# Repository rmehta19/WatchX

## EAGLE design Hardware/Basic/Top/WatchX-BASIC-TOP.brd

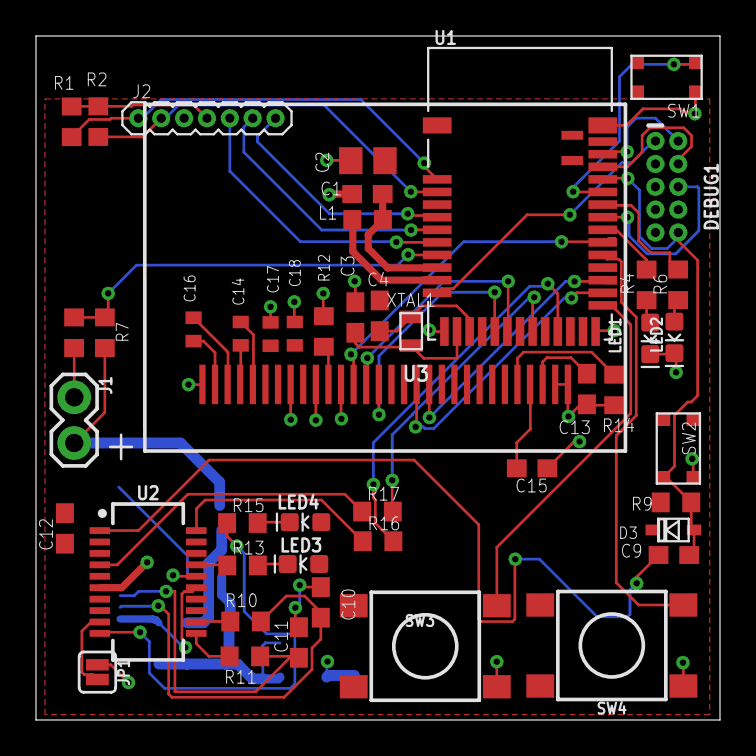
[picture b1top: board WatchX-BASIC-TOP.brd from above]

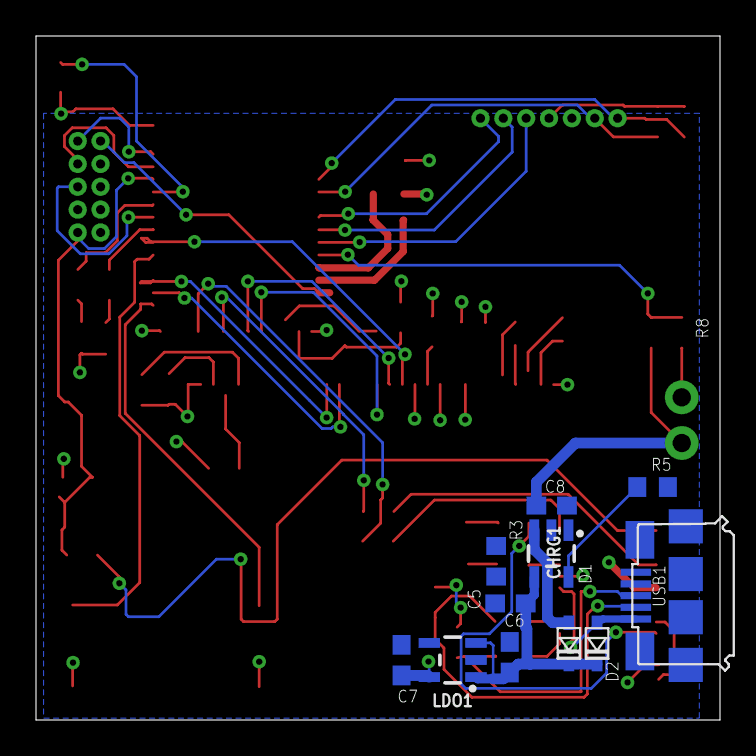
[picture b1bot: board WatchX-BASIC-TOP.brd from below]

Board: 2 copper layers, 38.0 x 38.0 mm, 58 parts (11 on the bottom side), 55 nets.

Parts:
C1, C6, C7: 1u; C0603
C2: 10u; C0805
C3, C4: C0603
C5, C8: 4.7u; C0603
C9, C12: 100n; C0603
C10, C11: 47p; C0603
C13: 10uF; C0603
C14, C16, C17, C18: 2.2uF; C0402
C15: 2.2uF; C0603
CHRG1: MCP73831; SOT23-5
D1, D2, D3: USC
DEBUG1: CORTEX_DEBUG_PTH; 2X5-PTH-1.27MM
J1: 1X02
J2: 1X07_1.27MM
JP1: SMT-JUMPER_2_NO_SILK
L1: 10u; L0603
LDO1: MIC5504; SOT23-5
LED1, LED3: RED; LED-0603
LED2: BLUE; LED-0603
LED4: YELLOW; LED-0603
R1, R2, R9, R12: 10k; R0603
R3, R7, R8: 100k; R0603
R4, R6, R13, R15: 1k; R0603
R5: 5k; R0603
R10, R11: 27; R0603
R14: 390k; R0603
R16, R17: R0603
SW1, SW2: BUTTON-GULLWING
SW3, SW4: SWITCH.MOM; TACTILE_SWITCH_SMD_6.2MM_TALL
U1: NRF52832_MODULE_MDBT42; BLE_MODULE_RAYTAC_MDBT42
U2: FT231XS; SSOP20_L
U3: UG-2864HSWEG01_0.96IN_NO-WRAPAROUND
USB1: USB.MICRO-BIGGERPADS; USB-MICRO-01.BIGGERPADS
XTAL1: 32.768kHz; 2-SMD.NOLEAD.2.0MMTO1.2MM

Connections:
3.3V: C2.2, C7.1, C12.2, C17.2, C18.2, D3.-, DEBUG1.1, J2.4, LDO1.5, LED3.A, LED4.A, R1.2, R2.2, R9.2, U1.11, U2.3, U2.14, U3.6, U3.9
!CTS: JP1.2, U2.9
A4/PPG: J2.7, U1.5
A5/TIA: J2.6, U1.6
A7/BATT: R7.1, R8.2, U1.8
D3/RESET.OLED: U1.17, U3.14
D4/DC.OLED: U1.16, U3.15
D11/SW1: SW3.A1, U1.25
D15/SW2: SW4.A1, U1.29
D16/CS.OLED: U1.30, U3.13
D27/CHRG.STAT: CHRG1.1, R3.1
D30/LED.CTRL: J2.5, U1.7
DFU: SW1.3, U1.34
DTR: C9.1, U2.1
GND: C1.2, C2.1, C3.1, C4.2, C5.1, C6.1, C7.2, C8.2, C10.1, C11.2, C12.1, C13.1, C15.1, C17.1, C18.1, CHRG1.2, DEBUG1.3, DEBUG1.5, DEBUG1.7, DEBUG1.9, J1.1, J2.3, JP1.1, LDO1.2, LED1.C, LED2.C, R5.1, R8.1, R12.1, R14.2, SW1.1, SW2.3, SW3.B1, SW3.B2, SW4.B1, SW4.B2, U1.1, U1.12, U1.24, U1.39, U2.6, U2.16, U3.1, U3.8, U3.10, U3.12, U3.29, U3.30, USB1.5, USB1.S1, USB1.S2, USB1.S3, USB1.S4, USB1.S5, USB1.S6
LED1: R4.2, U1.31
LED2: R6.2, U1.33
MOSI: U1.27, U3.19
unnamed: R12.2, U3.11
unnamed: R14.1, U3.26
unnamed: C16.2, U3.2
unnamed: C3.2, U1.13, XTAL1.P$1
unnamed: C16.1, U3.3
unnamed: C4.1, U1.14, XTAL1.P$2
unnamed: C14.2, U3.4
unnamed: C14.1, U3.5
unnamed: LED1.A, R4.1
unnamed: LED2.A, R6.1
unnamed: L1.1, U1.10
unnamed: C1.1, L1.2, U1.9
unnamed: C13.2, U3.28
unnamed: C15.2, U3.27
unnamed: CHRG1.5, R5.2
unnamed: R10.2, U2.12
unnamed: R11.2, U2.11
unnamed: LED3.C, R13.2
unnamed: LED4.C, R15.2
RESET: C9.2, D3.+, DEBUG1.10, R9.1, SW2.1, U1.35
RXD.FT: R17.1, U2.4
RXD.NRF: R16.2, U1.21
RXLED: R13.1, U2.17
SCK: U1.26, U3.18
SCL: J2.2, R2.1, U1.3
SDA: J2.1, R1.1, U1.2
SWCLK: DEBUG1.4, U1.36
SWDIO: DEBUG1.2, U1.37
SWO: DEBUG1.6, U1.32
TXD.FT: R16.1, U2.20
TXD.NRF: R17.2, U1.19
TXLED: R15.1, U2.10
USB+: C11.1, R11.1, USB1.3
USB-: C10.2, R10.1, USB1.2
VIN: C5.2, C6.2, CHRG1.4, D1.-, D2.-, LDO1.1, LDO1.3, R3.2
VLIPO: C8.1, CHRG1.3, D1.+, J1.2, R7.2
V_USB: D2.+, U2.15, USB1.1

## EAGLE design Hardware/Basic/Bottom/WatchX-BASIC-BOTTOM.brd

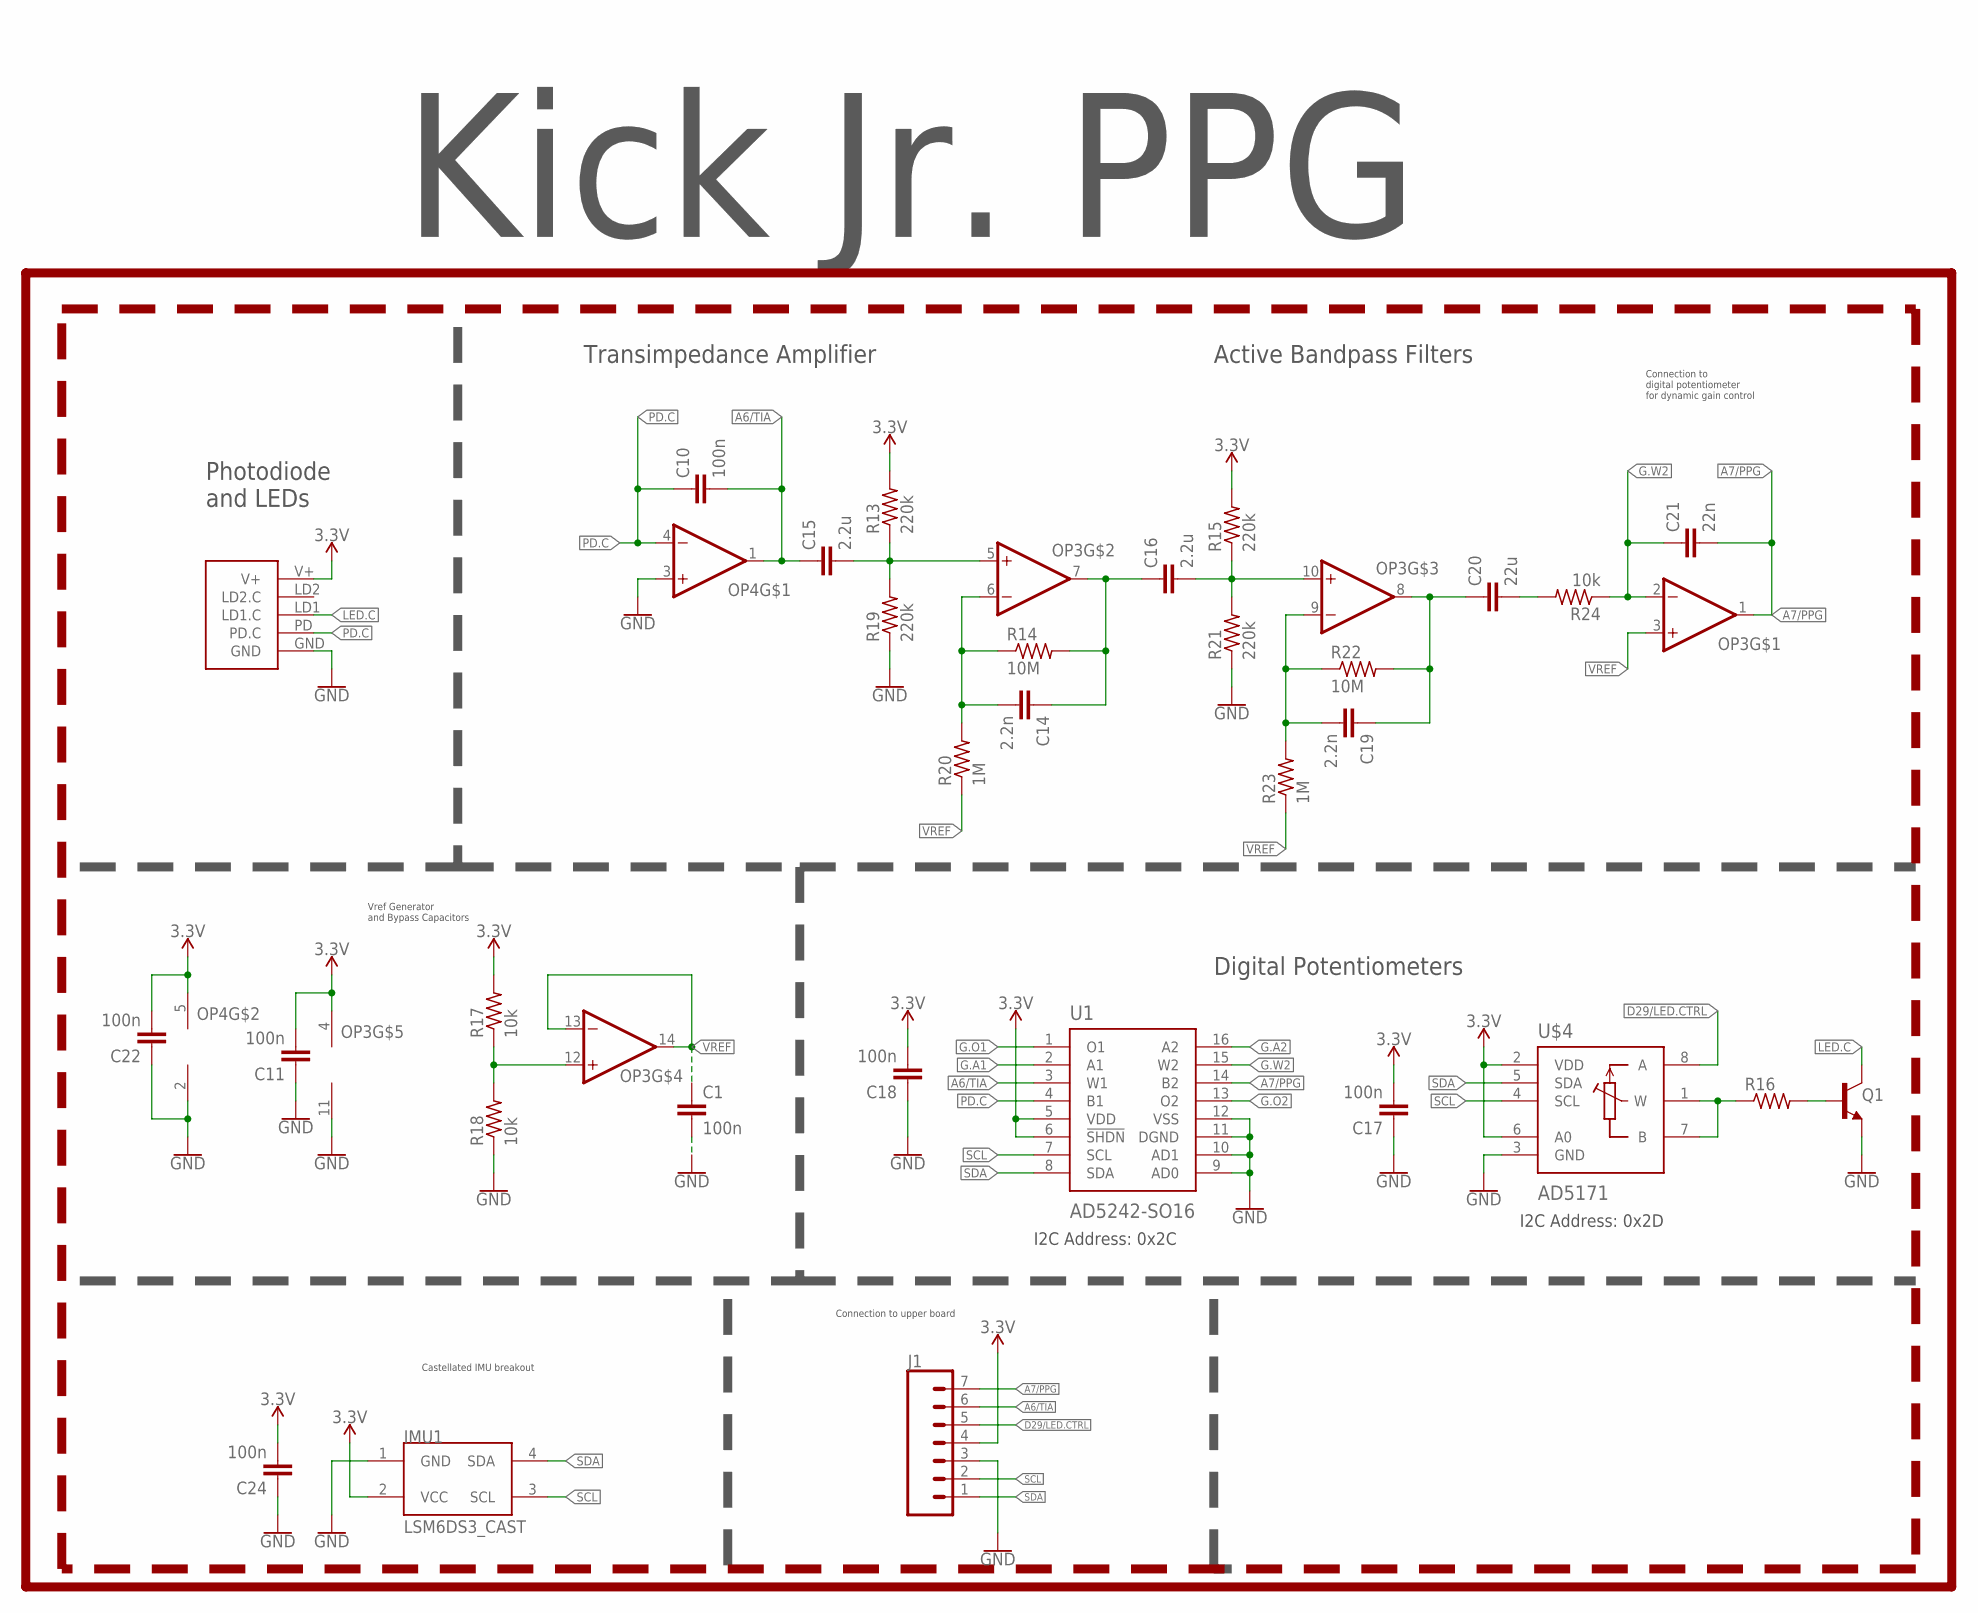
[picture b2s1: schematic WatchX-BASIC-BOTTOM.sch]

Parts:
C1, C10, C11, C17, C18, C22, C24: 100n; C0603
C14, C19: 2.2n; C0603
C15, C16: 2.2u; C0603
C20: 22u; C0603
C21: 22n; C0603
IMU1: LSM6DS3_CAST
J1: CONN_07-1.27MM; 1X07_1.27MM
OP3: OP-QUAD-SO14; SO14
OP4: OP-SINGLEOT; SOT23-5
Q1: NPN-GENERIC; SOT23-3
R13, R15, R19, R21: 220k; R0603
R14, R22: 10M; R0603
R16: RESISTOR0603; R0603
R17, R18: 10k; R0402
R20, R23: 1M; R0603
R24: 10k; R0603
U1: AD5242-SO16; SO16
U$3: PPG.MODULE.2
U$4: AD5171; SOT-23-8

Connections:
3.3V: C11.2, C17.2, C18.2, C22.2, C24.2, IMU1.2 (VCC), J1.4, OP3.4 (V+), OP4.5 (V+), R13.2, R15.2, R17.2, U1.5 (VDD), U1.6 (!SHDN), U$3.V+, U$4.2 (VDD), U$4.6 (A0)
A6/TIA: C10.2, C15.1, J1.6, OP4.1 (OUT), U1.3 (W1)
A7/PPG: C21.2, J1.7, OP3.1 (OUT), U1.14 (B2)
D29/LED.CTRL: J1.5, U$4.8 (A)
G.A1: U1.2 (A1)
G.A2: U1.16 (A2)
G.O1: U1.1 (O1)
G.O2: U1.13 (O2)
G.W2: C21.1, OP3.2 (-IN), R24.1, U1.15 (W2)
GND: C1.2, C11.1, C17.1, C18.1, C22.1, C24.1, IMU1.1 (GND), J1.3, OP3.11 (V-), OP4.2 (V-), OP4.3 (+IN), Q1.2 (E), R18.1, R19.1, R21.1, U1.9 (AD0), U1.10 (AD1), U1.11 (DGND), U1.12 (VSS), U$3.GND, U$4.3 (GND)
LED.C: Q1.3 (C), U$3.LD1 (LD1.C)
unnamed: Q1.1 (B), R16.2
unnamed: R16.1, U$4.1 (W), U$4.7 (B)
unnamed: OP3.12 (+IN), R17.1, R18.2
unnamed: C15.2, OP3.5 (+IN), R13.1, R19.2
unnamed: C14.2, OP3.6 (-IN), R14.1, R20.2
unnamed: C14.1, C16.1, OP3.7 (OUT), R14.2
unnamed: C16.2, OP3.10 (+IN), R15.1, R21.2
unnamed: C19.2, OP3.9 (-IN), R22.1, R23.2
unnamed: C19.1, C20.1, OP3.8 (OUT), R22.2
unnamed: C20.2, R24.2
PD.C: C10.1, OP4.4 (-IN), U1.4 (B1), U$3.PD (PD.C)
SCL: IMU1.3 (SCL), J1.2, U1.7 (SCL), U$4.4 (SCL)
SDA: IMU1.4 (SDA), J1.1, U1.8 (SDA), U$4.5 (SDA)
VREF: C1.1, OP3.3 (+IN), OP3.13 (-IN), OP3.14 (OUT), R20.1, R23.1

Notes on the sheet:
Photodiode and LEDs
Active Bandpass Filters
Digital Potentiometers
Transimpedance Amplifier
I2C Address: 0x2C
I2C Address: 0x2D
Connection to digital potentiometer for dynamic gain control
Connection to upper board
Castellated IMU breakout
Vref Generator and Bypass Capacitors
Kick Jr. PPG

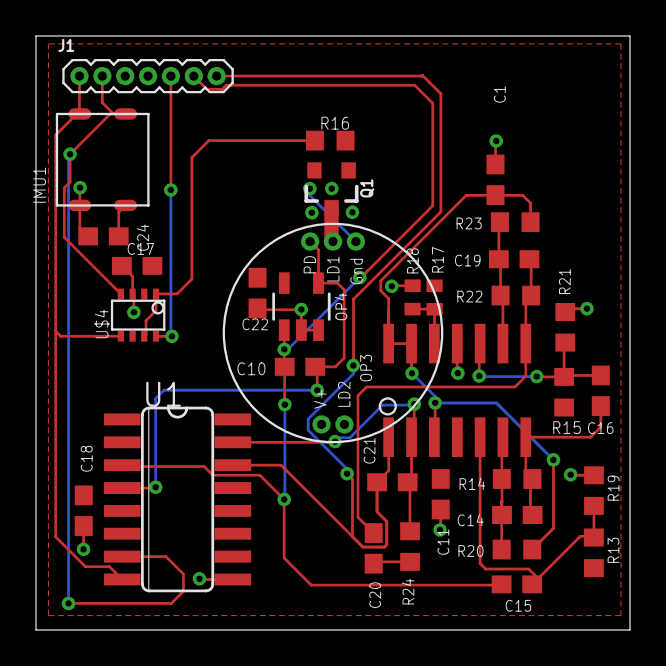
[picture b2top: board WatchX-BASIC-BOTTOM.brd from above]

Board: 2 copper layers, 33.0 x 33.0 mm, 33 parts (0 on the bottom side), 21 nets.

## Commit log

2020-06-30 features
2020-07-01 firmware
2020-07-01 hardware
2020-07-08 followed along with Take 001
2020-07-13 changes up to take 003
2020-07-21 edits through end of Take 008 video
